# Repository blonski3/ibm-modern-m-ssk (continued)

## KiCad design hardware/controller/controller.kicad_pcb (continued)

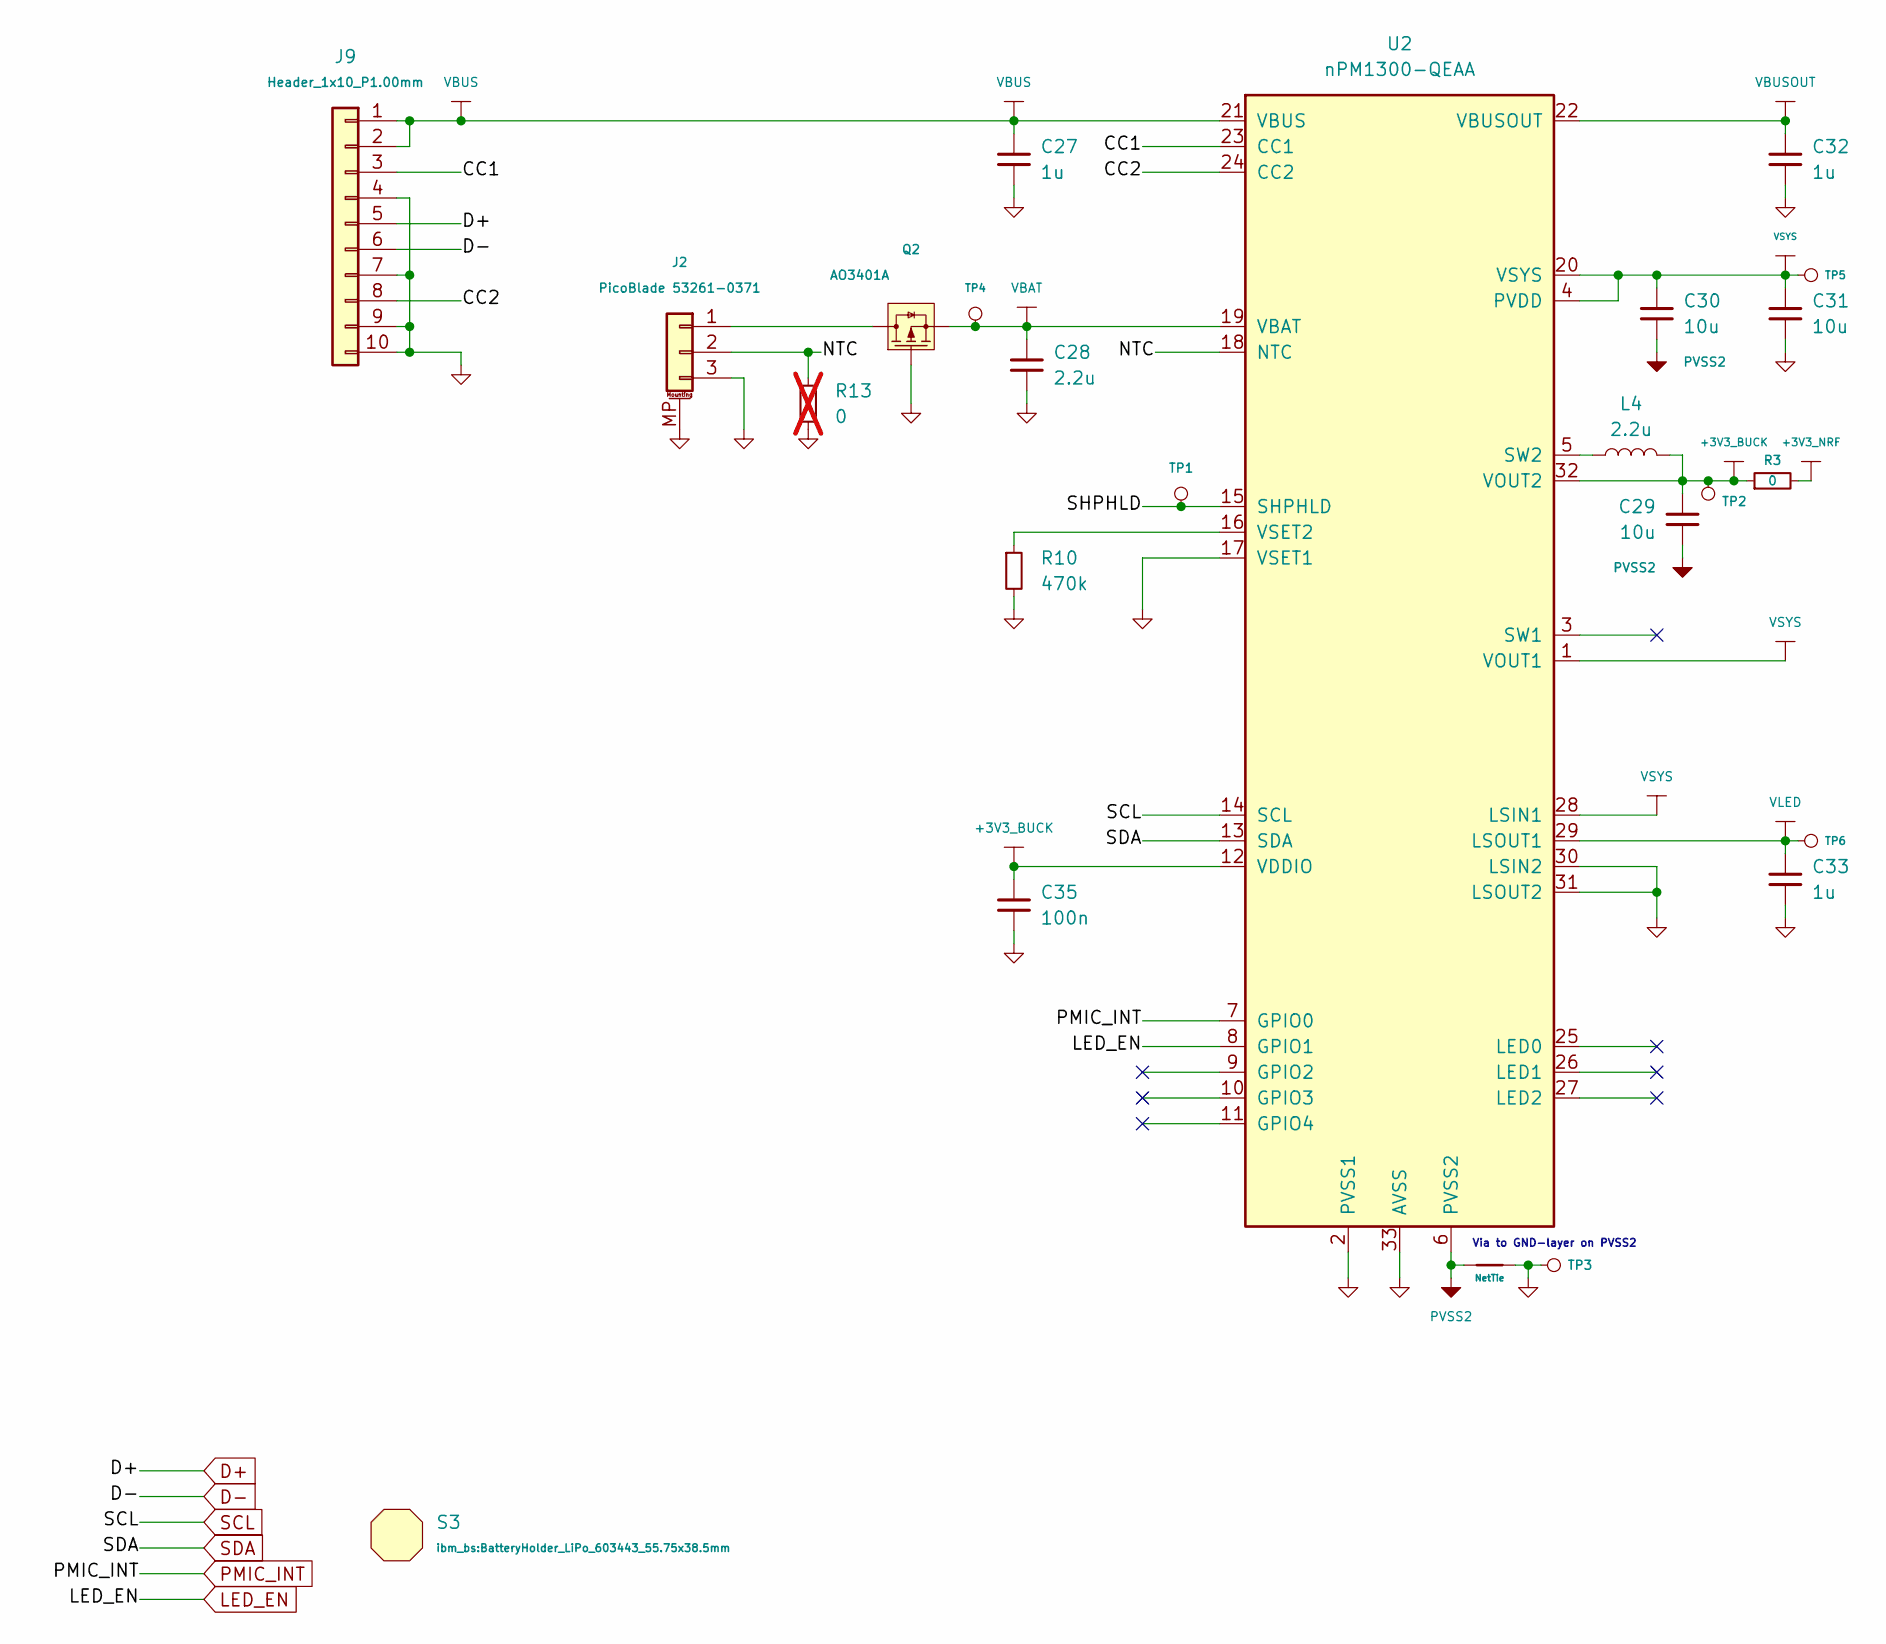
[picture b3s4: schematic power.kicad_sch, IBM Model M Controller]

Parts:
C27, C32, C33: 1u; C_0603_1608Metric; PART NUMBER CL10A105KB8NNNC; LCSC Part C15849
C28: 2.2u; C_0603_1608Metric; PART NUMBER CL10A225KO8NNNC; LCSC Part C23630
C29, C30, C31: 10u; C_0603_1608Metric; PART NUMBER CL10A106KP8NNNC; LCSC Part C19702
C35: 100n; C_0603_1608Metric; PART NUMBER CC0603KRX7R9BB104; LCSC Part C14663
J2: PicoBlade 53261-0371; Molex_PicoBlade_53261-0371_1x03-1MP_P1.25mm_Horizontal; PART NUMBER 53261-0371; LCSC Part C293630
J9: Header_1x10_P1.00mm; PinHeader_1x10_P1.00mm_Vertical
L4: 2.2u; L_1008_2520Metric; LCSC Part C5349606
NT1: NetTie; NetTie-2_SMD_Via0.45mm
Q2: AO3401A; SOT-23; PART NUMBER AO3401A; LCSC Part C15127
R3: 0; R_0603_1608Metric; PART NUMBER 0603WAF0000T5E; LCSC Part C21189
R10: 470k; R_0603_1608Metric; PART NUMBER 0603WAF4703T5E; LCSC Part C23178
R13: 0; R_0603_1608Metric; PART NUMBER 0603WAF0000T5E; LCSC Part C21189; not fitted
S3: Mechanical_Shape; BatteryHolder_LiPo_603443_55.75x38.5mm
TP1, TP2, TP3, TP4, TP5, TP6: TestPoint; TestPoint_0.75
U2: nPM1300-QEAA; Nordic_QFN50P500X500X90-33N; LCSC Part C7466043

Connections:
+3V3_BUCK: C29.1, C35.1, L4.2, R3.1, TP2.1 (1_1), U2.12 (VDDIO), U2.32 (VOUT2); also elsewhere on the board
+3V3_NRF: R3.2; also elsewhere on the board
/Power/CC1: J9.3, U2.23 (CC1)
/Power/CC2: J9.8, U2.24 (CC2)
/Power/NTC: J2.2, R13.1, U2.18 (NTC)
/Power/SHPHLD: TP1.1 (1_1), U2.15 (SHPHLD)
D+: J9.5; also elsewhere on the board
D-: J9.6; also elsewhere on the board
GND: C27.2, C28.2, C31.2, C32.2, C33.2, C35.2, J2.3, J2.MP (MountPin), J9.4, J9.7, J9.9, J9.10, NT1.1, Q2.1 (G), R10.2, R13.2, TP3.1 (1_1), U2.2 (PVSS1), U2.17 (VSET1), U2.30 (LSIN2), U2.31 (LSOUT2), U2.33 (AVSS); also elsewhere on the board
LED_EN: U2.8 (GPIO1); also elsewhere on the board
unnamed: J2.1, Q2.3 (D)
unnamed: L4.1, U2.5 (SW2)
unnamed: R10.1, U2.16 (VSET2)
PMIC_INT: U2.7 (GPIO0); also elsewhere on the board
PVSS2: C29.2, C30.2, NT1.2, U2.6 (PVSS2)
SCL: U2.14 (SCL); also elsewhere on the board
SDA: U2.13 (SDA); also elsewhere on the board
VBAT: C28.1, Q2.2 (S), TP4.1 (1_1), U2.19 (VBAT)
VBUS: C27.1, J9.1, J9.2, U2.21 (VBUS)
VBUSOUT: C32.1, U2.22 (VBUSOUT); also elsewhere on the board
VLED: C33.1, TP6.1 (1_1), U2.29 (LSOUT1); also elsewhere on the board
VSYS: C30.1, C31.1, TP5.1 (1_1), U2.1 (VOUT1), U2.4 (PVDD), U2.20 (VSYS), U2.28 (LSIN1); also elsewhere on the board

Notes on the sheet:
Via to GND-layer on PVSS2

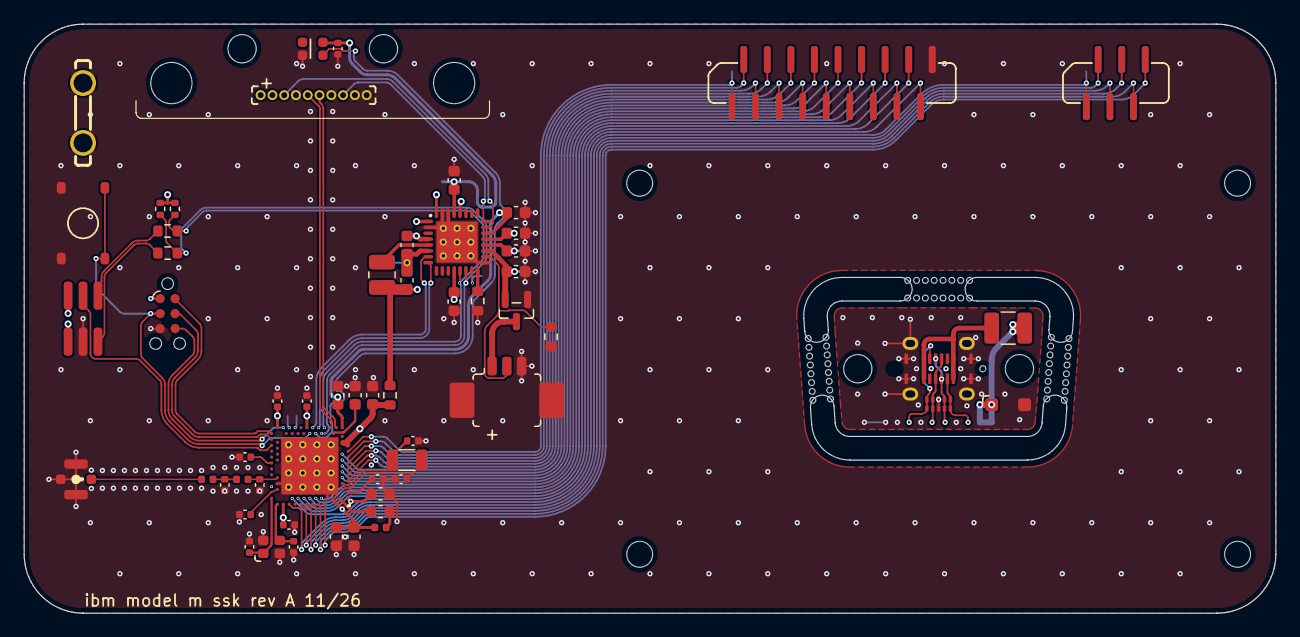
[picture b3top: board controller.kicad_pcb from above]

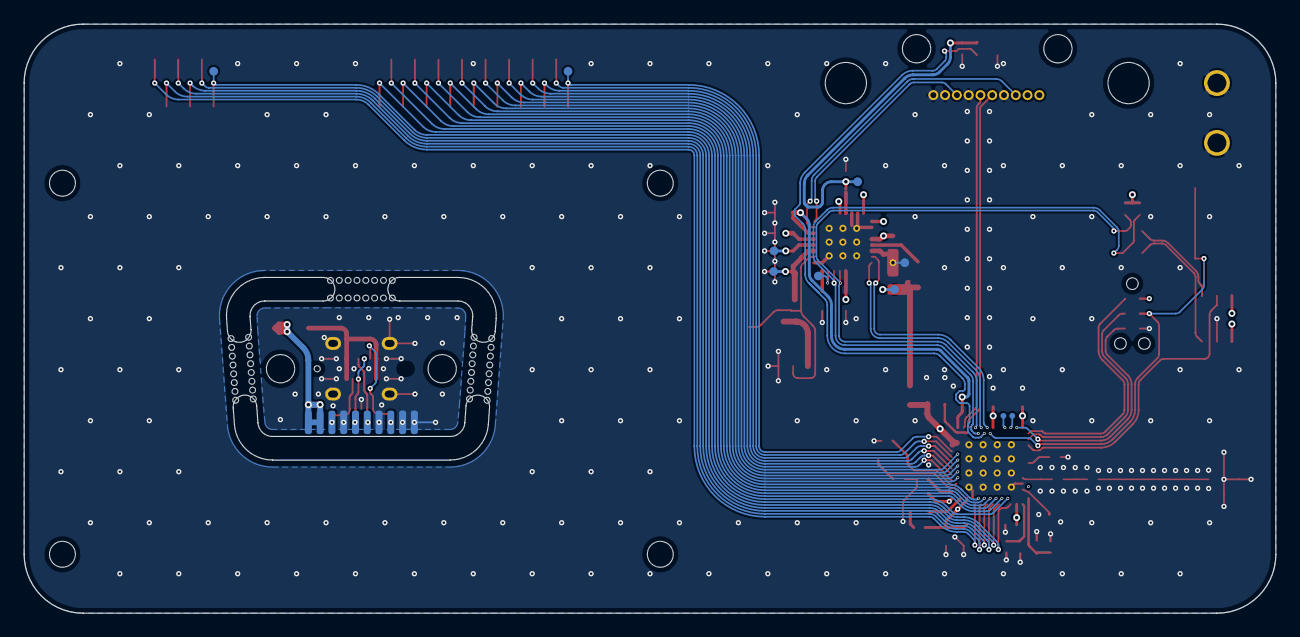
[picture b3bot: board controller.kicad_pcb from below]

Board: 4 copper layers, 106.2 x 50.0 mm, 73 parts (11 on the bottom side), 76 nets.

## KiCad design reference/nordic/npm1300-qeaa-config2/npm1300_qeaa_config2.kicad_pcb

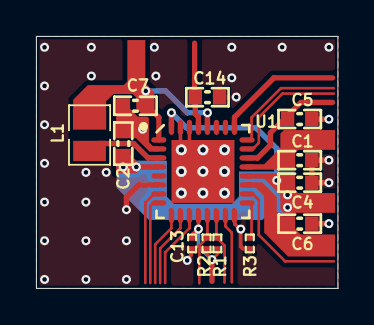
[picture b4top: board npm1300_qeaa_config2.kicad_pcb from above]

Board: 4 copper layers, 16.8 x 14.0 mm, 14 parts (0 on the bottom side), 13 nets.

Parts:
C1, C5, C14: 1.0µF; CAPC1608X06L
C2, C4, C7: 10µF; CAPC1608X06L
C6: 2.2µF; CAPC1608X06L
C13: 100nF; CAPC0603X03L_C
L1: 2.2µH; INDC2016X10N
NT1: Net tie; 2 PIN STARPOINT
R1, R2: 10k; RESC0603X03L_C
R3: 47k; RESC0603X03L_C
U1: nPM1300-QEAA; Nordic_QFN50P500X500X90-33N

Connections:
GND: C1.1, C4.1, C5.1, C6.1, C13.2, C14.1, NT1.1, R3.2, U1.6, U1.16, U1.30, U1.31, U1.33
LSOUT1: C14.2, U1.29
PVSS1: C2.1, C7.1, NT1.2, U1.2
SCL: R1.1, U1.14
SDA: R2.1, U1.13
SW1: L1.2, U1.3
VBAT: C6.2, U1.19
VBUSIN: C1.2, U1.21
VBUSOUT: C5.2, U1.22
VDDIO: C13.1, R1.2, R2.2, U1.12
VOUT1: C7.2, L1.1, U1.1, U1.28
VSET1: R3.1, U1.17
VSYS: C2.2, C4.2, U1.4, U1.20, U1.32

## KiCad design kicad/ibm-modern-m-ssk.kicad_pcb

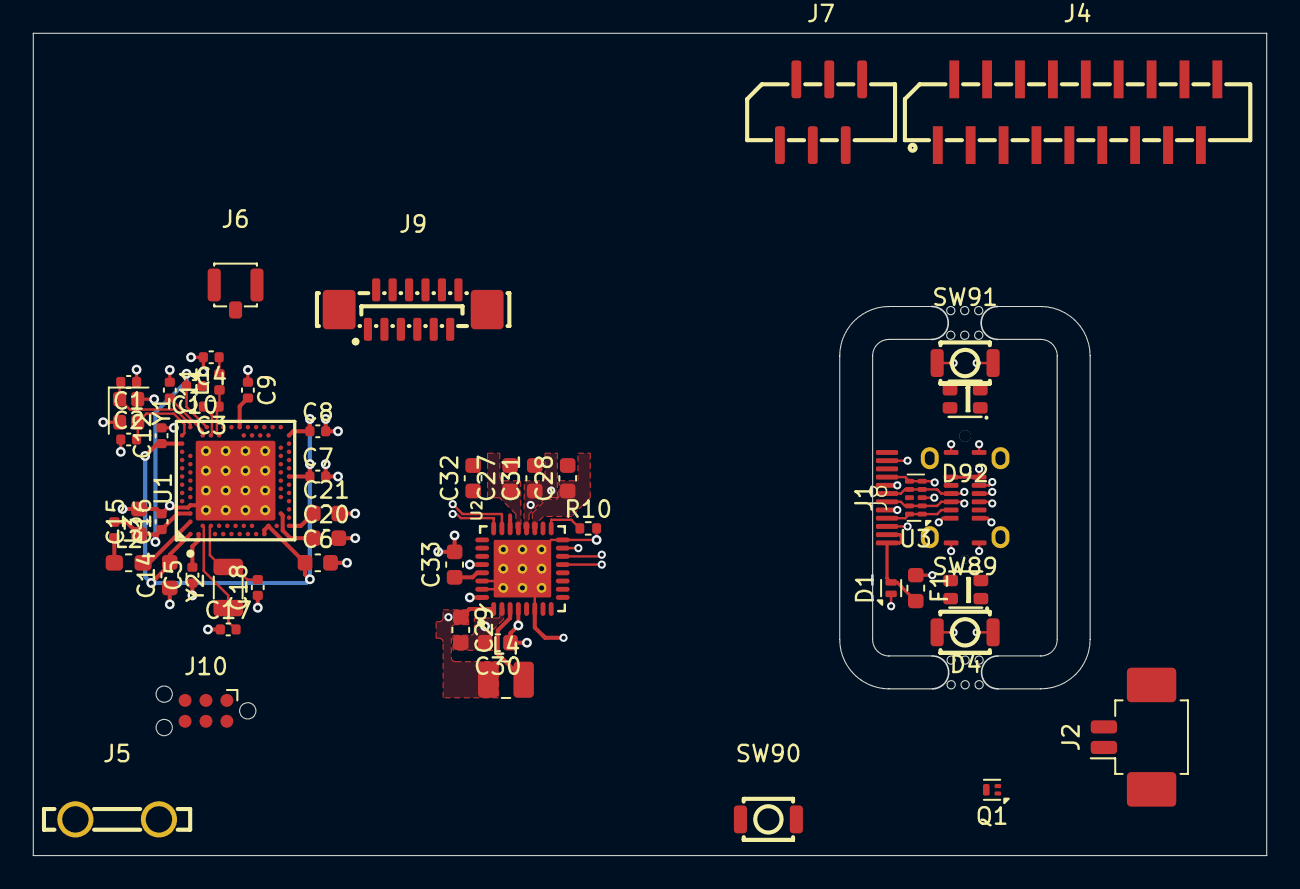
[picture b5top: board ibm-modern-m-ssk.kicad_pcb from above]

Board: 4 copper layers, 75.0 x 50.0 mm, 53 parts (0 on the bottom side), 35 nets.

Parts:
C1, C2, C17, C18: 12p; C_0402_1005Metric
C3: 0.8p; C_0402_1005Metric
C4: 0.5p; C_0402_1005Metric
C5, C7, C8, C12: 100n; C_0402_1005Metric
C6, C20, C21: 4.7u; C_0603_1608Metric
C9: 820p; C_0402_1005Metric
C10: NC; C_0402_1005Metric
C11: 100p; C_0402_1005Metric
C14, C15, C27, C32, C33: 1u; C_0603_1608Metric
C16: 47n; C_0402_1005Metric
C28: 2.2u; C_0603_1608Metric
C29, C30, C31: 10u; C_0603_1608Metric
D1: PESDNC2FD5VB; Diodes_DFN1006-2
D4, D92: rgb; WS2812C-2020-V1
F1: BSMD0603L-150; Fuse_0603_1608Metric
J1: TYPE-C-31-D-06; USB-C-SMD_TYPE-C-31-D-06
J2: Molex PicoBlade; Molex_PicoBlade_53261-0271_1x02-1MP_P1.25mm_Horizontal
J4: AFB10-S18LCA-00; FPC-SMD_18P-P1.00_AFB10-S18LCA-00
J5: 726386-2; CONN-TH_726386-2
J6: Conn_Coaxial_Small; IPEX-SMD_3P-L2.6-W2.6-LS3.0_ZCF-CF0001-0002IPEX
J7: AFB10-S06LCA-00; FPC-SMD_6P-P1.00_AFB10-S6LCA-00
J8: FPC_12P_0.5mm
J9: AFC11-S12ICA-00; CONN-SMD-12P_AFC11-S12ICA-00
J10: TC2030; Tag-Connect_TC2030-IDC-NL_2x03_P1.27mm_Vertical
L1: 4.7n; L_0402_1005Metric
L2: 10u; L_0603_1608Metric_Pad1.05x0.95mm_HandSolder
L3: 15n; L_0402_1005Metric
L4: 2.2u; L_1008_2520Metric
Q1: PMZB350UPE,315; DFN1006-3
R10: 470k; R_0402_1005Metric
SW89, SW90, SW91: SW_Push; KEY-SMD_B3U-1000PM
U1: NRF52840; AQFN50P700X700X85_HS-74N
U2: nPM1300-QEAA; Nordic_QFN50P500X500X90-33N
U3: TPD4E05U06DQAR; USON-10_2.5x1.0mm_P0.5mm
Y1: 32MHz; Crystal_SMD_2016-4Pin_2.0x1.6mm
Y2: 32.768 kHz; Crystal_SMD_3215-2Pin

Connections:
/daughterboard/BT_PAIR: J8.3, J9.3, SW89.1
/daughterboard/CC1: J1.A5 (CC1), J8.4, J9.4, U2.23 (CC1), U3.1 (D1+), U3.10 (NC)
/daughterboard/CC2: J1.B5 (CC2), J8.9, J9.9, U2.24 (CC2), U3.5 (D2-), U3.6 (NC)
/daughterboard/LED_DATA: D4.3 (DIN), J8.10, J9.10
/daughterboard/SHPHLD: J8.11, J9.11, SW91.1, U2.15 (SHPHLD)
/motherboard/ANTENNA: C4.1, J6.1 (In), L1.2
/motherboard/DEC4: C10.2, C15.1, C16.1, L3.1, U1.B5 (DEC4), U1.E24 (DEC6)
/motherboard/SWCLK: J10.4, U1.AA24 (SWDCLK)
/motherboard/SWDIO: J10.2, U1.AC24 (SWDIO)
D+: J1.A6 (D+), J1.B6 (D+), J8.6, J9.6, U1.AD6 (D+), U3.2 (D1-), U3.9 (NC)
D-: J1.A7 (D-), J1.B7 (D-), J8.7, J9.7, U1.AD4 (D-), U3.4 (D2+), U3.7 (NC)
GND: C1.1, C2.1, C3.2, C4.2, C5.1, C6.2, C7.2, C8.2, C9.2, C10.1, C11.1, C12.2, C14.1, C15.2, C16.2, C17.1, C18.1, C20.2, C21.2, C27.2, C28.2, C31.2, C32.2, C33.2, D1.1 (A1), D4.2 (VSS), D92.2 (VSS), J1.A1 (GND), J1.A12 (GND), J1.B1 (GND), J1.B12 (GND), J2.2, J5.1, J6.2 (Ext), J8.5, J8.8, J9.5, J9.8, J10.3, J10.5, Q1.1 (G), R10.2, SW89.2, SW90.2, SW91.2, U1.74 (GND), U1.B7 (VSS), U1.F23 (VSS_PA), U2.6 (PVSS2), U2.16 (VSET2), U2.30 (LSIN2/VINLDO2), U2.31 (LSOUT2/VOUTLDO2), U2.33 (AVSS), U3.3 (GND), U3.8 (GND), Y1.2, Y1.4
unnamed: D4.1 (DOUT), D92.3 (DIN)
unnamed: F1.1, J1.A4 (VBUS), J1.A9 (VBUS), J1.B4 (VBUS), J1.B9 (VBUS)
unnamed: L2.1, L3.2
unnamed: J2.1, Q1.2 (S)
unnamed: C3.1, L1.1, U1.H23 (ANT)
unnamed: L2.2, U1.B3 (DCC)
unnamed: C5.2, U1.C1 (DEC1)
unnamed: C11.2, U1.D23 (DEC3)
unnamed: C9.1, U1.N24 (DEC5)
unnamed: C20.1, U1.AC5 (DECUSB)
unnamed: C17.2, U1.D2 (P0.00/XL1), Y2.2
unnamed: C18.2, U1.F2 (P0.01/XL2), Y2.1
unnamed: C1.2, U1.B24 (XC1), Y1.3
unnamed: C2.2, U1.A23 (XC2), Y1.1
unnamed: C33.1, U2.29 (LSOUT1/VOUTLDO1)
unnamed: L4.2, U2.3 (SW1)
unnamed: R10.1, U2.17 (VSET1)
PVSS1: C29.2, C30.2, U2.2 (PVSS1)
VBAT: C28.1, Q1.3 (D), U2.19 (VBAT)
VBUS: C27.1, D1.2 (A2), F1.2, J8.1, J8.2, J9.1, J9.2, U2.21 (VBUS)
VBUSOUT: C21.1, C32.1, U1.AD2 (VBUS), U2.22 (VBUSOUT)
VDD_NRF: C6.1, C7.1, C8.1, C12.1, C14.2, C29.1, J10.1, L4.1, U1.A22 (VDD), U1.AD14 (VDD), U1.AD23 (VDD), U1.B1 (VDD), U1.W1 (VDD), U1.Y2 (VDDH), U2.1 (VOUT1), U2.28 (LSIN1/VINLDO1)
VSYS: C30.1, C31.1, D4.4 (VDD), D92.4 (VDD), J8.12, J9.12, U2.4 (PVDD), U2.20 (VSYS), U2.32 (VOUT2)

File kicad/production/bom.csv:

Designator,Footprint,Quantity,Value,LCSC Part #
"C1, C17, C18, C2",0402,4,12p,C526985
"C10, C13, C22",0402,3,NC,~
C11,0402,1,100p,C106200
"C12, C5, C7, C8",0402,4,100n,C60474
"C14, C15, C27, C32, C33",0603,5,1u,C559769
C16,0402,1,47n,C327054
"C20, C21, C6",0603,3,4.7u,C277476
C28,0603,1,2.2u,C309478
"C29, C30, C31",0603,3,10u,C596327
C3,0402,1,0.8p,C326068
C4,0402,1,0.5p,C327230
C9,0402,1,820p,C726612
D2,LED-SMD_4P-L1.6-W1.5-TR-1,1,LED_RGB,C3029071
E1,SON-6_L1.4-W1.0-P0.50-TL_USBULC6-2M6,1,TPD2E001DRYR-TP,C2923399
J1,FPC-SMD_24P-P0.50_TF38-24S-0.5SV-830,1,TF38-24S-0.5SV(830),C3020653
J2,CONN-SMD_2P-P1.00_SM02B-SRSS-TB-LF-SN,1,S2B-PH-SM4-TB(LF)(SN),C160402
J5,CONN-TH_726386-2,1,726386-2,C305817
L1,0402,1,4.7n,C304335
L2,0603,1,10u,C86083
L3,0402,1,15n,C381880
L4,1008,1,2.2u,C5349606 
Q1,SOT-23-3_L2.9-W1.3-P1.90-LS2.4-BR,1,DMP2123LQ,C3647032
R1,0402,1,10k,C25744
R10,0402,1,470k,C25792
"R8, R9",0402,2,5.1k,C25905
SW90,SW-SMD_L3.9-W3.0-P4.45,1,SW_Push,C720477
U1,AQFN50P700X700X85_HS-74N,1,NRF52840,C190794
U2,Nordic_QFN50P500X500X90-33N,1,nPM1300-QEAA,C7466043
USBC1,USB-C_SMD-TYPE-C-31-M-12_1,1,TYPE-C-31-M-12,C165948
Y1,Crystal_SMD_2016-4Pin_2.0x1.6mm,1,32MHz,C255896
Y2,Crystal_SMD_3215-2Pin_3.2x1.5mm,1,32.768 kHz,C99010

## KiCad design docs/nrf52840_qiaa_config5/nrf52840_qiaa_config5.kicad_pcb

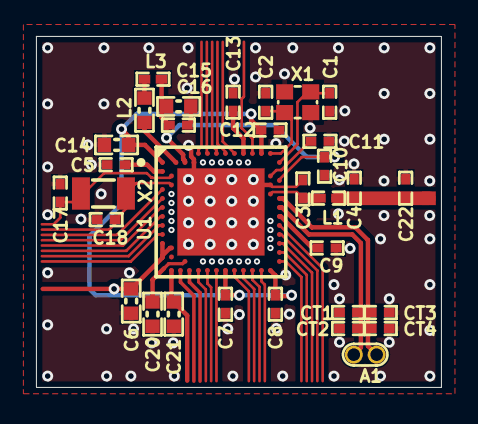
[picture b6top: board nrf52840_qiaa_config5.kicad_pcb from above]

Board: 4 copper layers, 22.5 x 19.5 mm, 32 parts (0 on the bottom side), 19 nets.

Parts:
A1: NFC Antenna; TP_2x1mm_TH
C1, C2, C17, C18: 12pF; CAPC1005X04L
C3: 0.8pF; CAPC1005X04L
C4: 0.5pF; CAPC1005X04L
C5, C7, C8, C12: 100nF; CAPC1005X04L
C6, C20, C21: 4.7µF; CAPC1608X06L
C9: 820pF; CAPC1005X04L
C10, C13, C22: N.C.; CAPC1005X04L
C11: 100pF; CAPC1005X04L
C14, C15: 1.0µF; CAPC1608X06L
C16: 47nF; CAPC1005X04L
CT1, CT2, CT3, CT4: Antenna dependent; CAPC1005X04L
L1: 4.7nH; INDC1005X04L
L2: 10µH; INDC1608X06L
L3: 15nH; INDC1005X04L
U1: nRF52840-QIAA; AQFN50P700X700X85_HS-74N
X1: 32MHz; BT-XTAL_2016
X2: 32.768kHz; XTAL_3215

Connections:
DEC1: C5.1, U1.C1
DEC3: C11.1, U1.D23
DEC4_6: C10.2, C15.2, C16.1, L3.1, U1.B5, U1.E24
GND: C1.2, C2.2, C3.1, C4.1, C5.2, C6.2, C7.2, C8.2, C9.2, C10.1, C11.2, C12.2, C13.2, C14.2, C15.1, C16.2, C17.2, C18.2, C20.2, C21.2, C22.2, CT1.2, CT2.2, CT3.1, CT4.1, U1.74, U1.B7, U1.F23, X1.2, X1.4
NFC1: A1.2, CT1.1, CT2.1, U1.L24
NFC2: A1.1, CT3.2, CT4.2, U1.J24
NetC3_2: C3.2, L1.1, U1.H23
NetC9_1: C9.1, U1.N24
NetC13_1: C13.1, U1.A18
NetC20_1: C20.1, U1.AC5
NetL2_1: L2.1, L3.2
NetL2_2: L2.2, U1.B3
P0.00/XL1: C17.1, U1.D2, X2.1
P0.01/XL2: C18.1, U1.F2, X2.2
RF: C4.2, C22.1, L1.2
VBUS: C21.1, U1.AD2
VDD_NRF: C6.1, C7.1, C8.1, C12.1, C14.1, U1.A22, U1.AD14, U1.AD23, U1.B1, U1.W1, U1.Y2
XC1: C1.1, U1.B24, X1.1
XC2: C2.1, U1.A23, X1.3

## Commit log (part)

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2026-01-26 Update LICENSE
2026-01-26 create kicad project
2026-01-26 library update
2026-01-26 create buckling spring footprint
2026-01-26 Update fp-info-cache
2026-01-26 Add KiCad project files for IBM Modern M SSK
    Added new KiCad project-related files: project state (.kicad_prl), updated project settings (.kicad_pro), and a backup ZIP. Updated fp-info-cache with new footprint information for 'ibm buckling spri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
2026-01-26 Add matrix schematic and update project structure
    Added new matrix.kicad_sch schematic file and integrated it as a subsheet in ibm-modern-m-ssk.kicad_sch. Updated project and schematic settings in ibm-modern-m-ssk.kicad_pro and adjusted selection fi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
2026-01-26 matrix update
2026-01-26 Add new symbols to schematic and update selection filter
    Added symbols for MCP73831-2-OT, USB_C_Receptacle_USB2.0_14P, R_Small, and MDBT50Q-1MV2 to ibm-modern-m-ssk.kicad_sch. Updated selection filter in ibm-modern-m-ssk.kicad_prl to enable all item types.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
2026-01-26 Add new KiCad backup files and clean up temp files
    Added several new backup ZIP files for the IBM Modern M SSK project. Removed auto-saved and lock files to clean up the project directory.
2026-01-27 Add new connectors and components to schematic
    Added symbols for Conn_01x02_Socket, Conn_02x06_Odd_Even, C_Small, Crystal_Small, LED_Small_Filled, and USBLC6-2P6 to ibm-modern-m-ssk.kicad_sch. Updated schematic to include these components. Added 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
2026-01-31 Schematic done
2026-02-01 Schematic Done v2
2026-02-01 Add KiCad autosave reference and backup zips
    Add kicad/#auto_saved_files# pointing to _autosave-ibm-modern-m-ssk.kicad_sch and include multiple timestamped backup ZIP archives under kicad/ibm-modern-m-ssk-backups (2026-01-31 to 2026-02-01). The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
2026-02-01 Add SW-SMD_L3.9-W3.0-P4.45 footprint
    Add new KiCad pretty module kicad/libraries/easyeda2kicad.pretty/SW-SMD_L3.9-W3.0-P4.45.kicad_mod. The footprint defines an SMD toggle switch with two rectangular pads (at ±2.18 mm, size 1.23×1.86 mm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
2026-02-01 Footprints & BOM done
2026-02-01 Rotate KiCad backups; update autosave list
    Add _autosave-matrix.kicad_sch to kicad/#auto_saved_files# and rotate ibm-modern-m-ssk backup archives: remove three older zips (..._000924.zip, ..._001918.zip, ..._004606.zip) and add three new ones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
2026-02-01 Update KiCad schematic, project files and backups
    Rotate backups, and adjust KiCad project/schematic files. Deleted kicad/#auto_saved_files# and removed an old backup; added two new ibm-modern-m-ssk backup zips. Updated kicad/ibm-modern-m-ssk.kicad_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
2026-02-05 Add LiPo STEP/module and backups, update schematic
    Add LiPo_603450_1200mAh STEP (3D) and corresponding .kicad_mod to the easyeda2kicad libraries, add two ibm-modern-m-ssk backup ZIPs, and update kicad/matrix.kicad_sch. Remove stale PCB lock file (~ib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
2026-02-05 Import complete KiCad PCB, schematic & footprint
    Add full KiCad PCB file (ibm-modern-m-ssk.kicad_pcb) including board setup, layers, nets and populated footprints (generated by pcbnew 9.0). Update project files (.kicad_prl, .kicad_pro, .kicad_sch) 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
2026-02-05 Clean up fp-info-cache and update checksum
    Remove numerous obsolete or duplicate footprint entries from kicad/fp-info-cache (multiple capacitor THT variants, several connector blocks including Hirose FX10, DEC PCBEdge, M.2 variants, Samtec Ed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
2026-02-07 Adjust KiCad schematic text properties
    Update kicad/ibm-modern-m-ssk.kicad_sch to standardize text formatting: increase several font sizes and thicknesses and tweak one label position for consistency. Add .gitignore entry to ignore kicad/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
2026-02-07 nrf52840_qiaa reference circuit
2026-02-07 nordic footprints update
2026-02-07 add nordic symbols & footprints
2026-02-07 Add nrf52840_qiaa KiCad library entries
    Register new KiCad libraries for the nRF52840 QIAA design: add a footprint library entry (nrf52840_qiaa) to kicad/fp-lib-table and a symbol library entry (nrf52840_qiaa_config5) to kicad/sym-lib-tabl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
2026-02-09 update mcu
2026-02-09 update lolololololololo
2026-02-13 update - change pmic to npm1300
2026-02-19 update - pcb layout
